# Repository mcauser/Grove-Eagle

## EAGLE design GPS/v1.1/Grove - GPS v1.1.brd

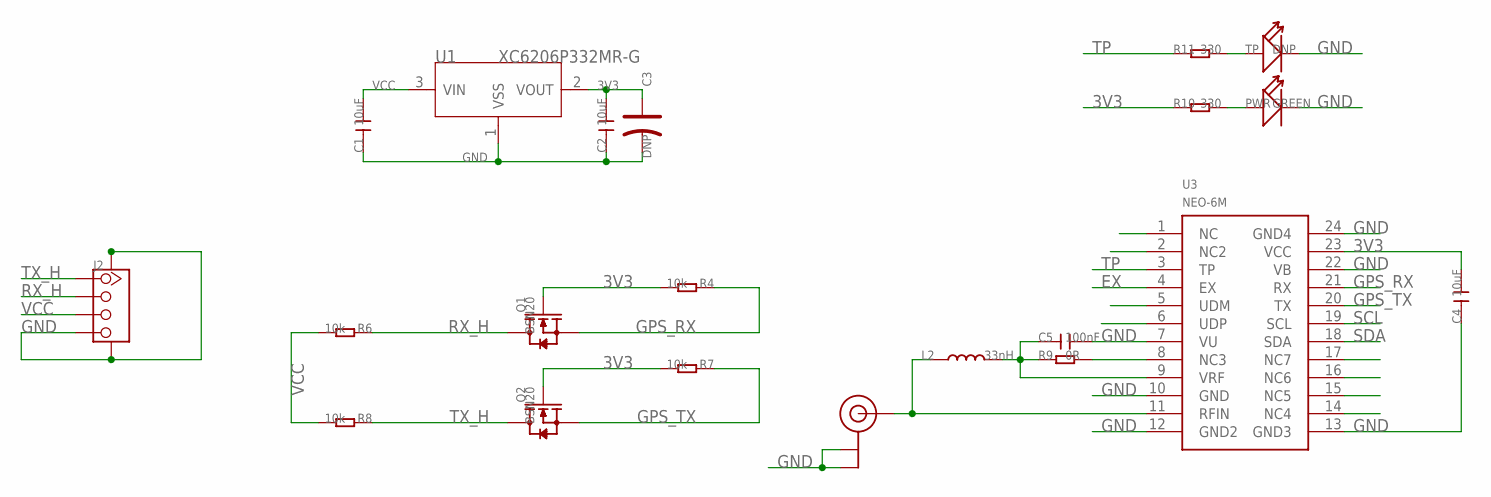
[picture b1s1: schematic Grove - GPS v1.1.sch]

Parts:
C1, C2, C4: 10uF; C0805
C3: DNP; AVX-A
C5: 100nF; C0603
J2: TWIG-4P-2.0-SMD-FEMALE-REINFORCE'DD'; 4P-SMD-2.0
L2: 33nH; L0603
PWR: GREEN; LED-0603
Q1, Q2: BSN20; SOT23
R4, R6, R7, R8: 10k; R0603
R9: 0R; R0603
R10, R11: 330; R0603
TP: DNP; LED-0603
U1: XC6206P332MR-G; SOT23
U3: NEO-6M; 28P-1.1-16.0X12.2
U4: U.FL

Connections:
3V3: C2.2, C3.+, C4.2, Q1.1 (G), Q2.1 (G), R4.2, R7.2, R10.1, U1.2 (VOUT), U3.23 (VCC)
EX: U3.4 (EX)
GND: C1.1, C2.1, C3.-, C4.1, C5.2, J2.4, J2.SS1, J2.SS2, PWR.-, TP.-, U1.1 (VSS), U3.7 (VU), U3.10 (GND), U3.12 (GND2), U3.13 (GND3), U3.22 (VB), U3.24 (GND4), U4.P$1 (GND), U4.P$2 (GND)
GPS_RX: Q1.2 (S), R4.1, U3.21 (RX)
GPS_TX: Q2.2 (S), R7.1, U3.20 (TX)
unnamed: L2.1, U3.11 (RFIN), U4.P$3 (SIGNAL)
unnamed: C5.1, L2.2, R9.1, U3.9 (VRF)
unnamed: PWR.+, R10.2
unnamed: R9.2, U3.8 (NC3)
unnamed: R11.2, TP.+
RX_H: J2.2, Q1.3 (D), R6.1
SCL: U3.19 (SCL)
SDA: U3.18 (SDA)
TP: R11.1, U3.3 (TP)
TX_H: J2.1, Q2.3 (D), R8.1
VCC: C1.2, J2.3, R6.2, R8.2, U1.3 (VIN)

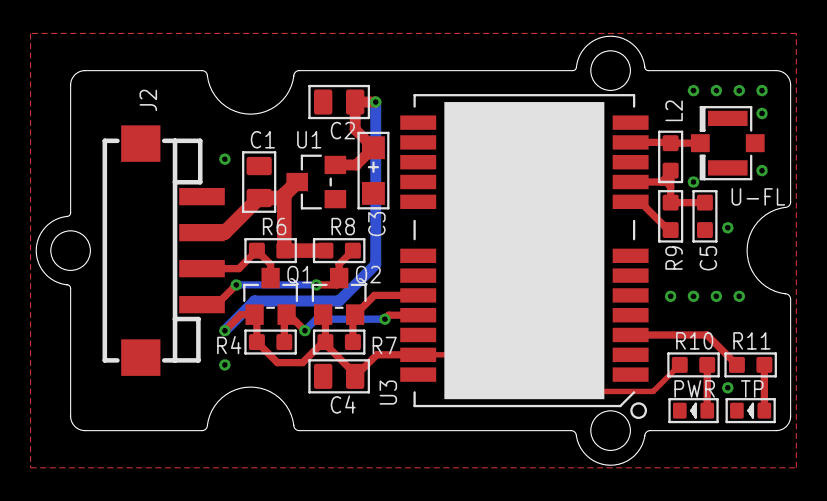
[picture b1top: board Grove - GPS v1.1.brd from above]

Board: 2 copper layers, 41.9 x 23.8 mm, 24 parts (2 on the bottom side), 13 nets.

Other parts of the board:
U$1: 2U-DIM-W/DRILL
U$2: OSHW_FILLX200_NOTEXT
U$4: TWIGLOGO

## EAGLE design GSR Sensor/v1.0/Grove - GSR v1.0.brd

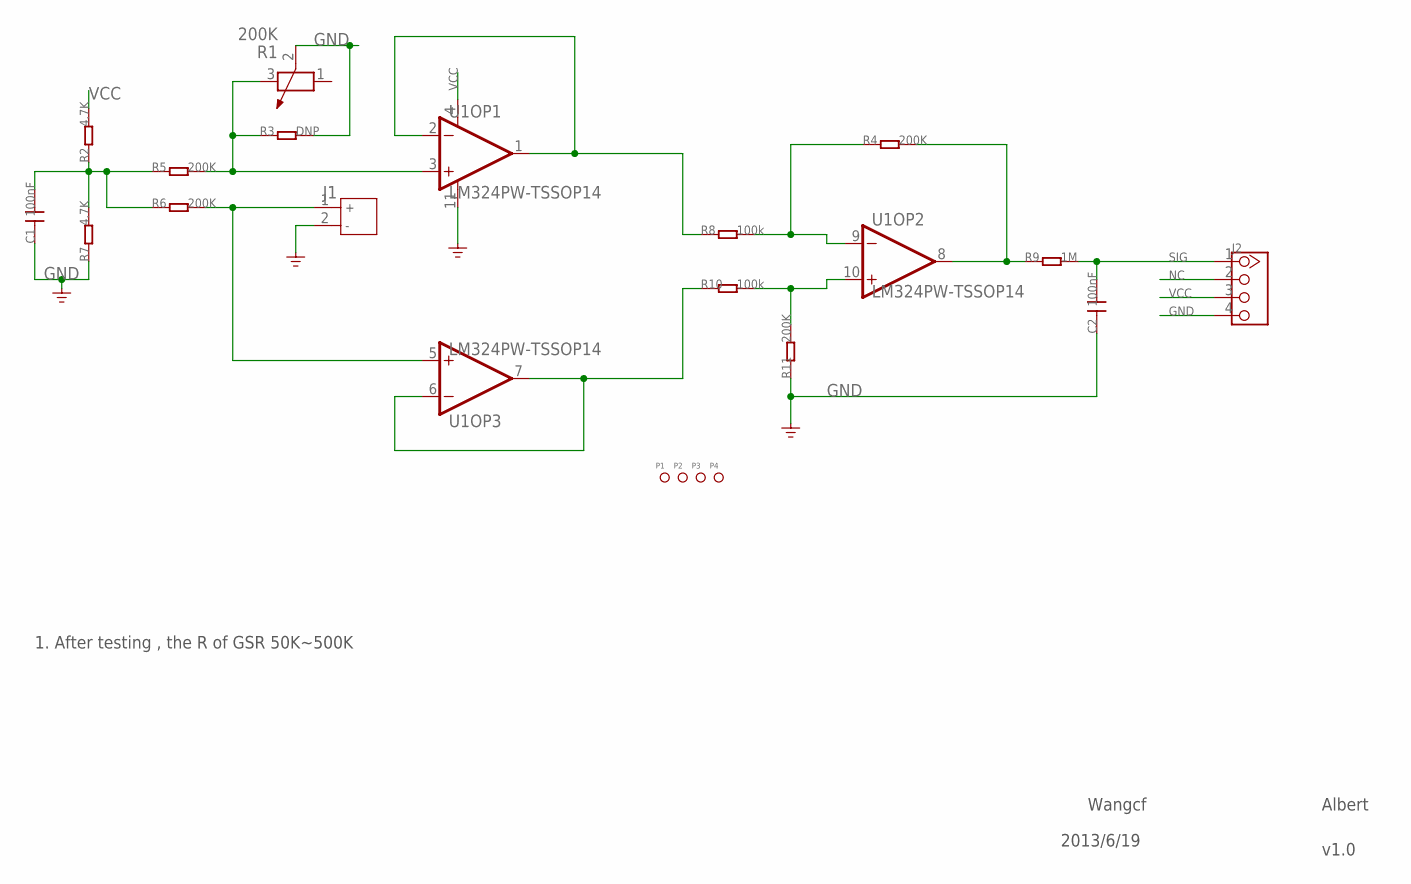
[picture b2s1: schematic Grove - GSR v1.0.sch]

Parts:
C1, C2: 100nF; 0603
J1: JACK-JST-2P-PW'2.0'; JST-2.0
J2: TWIG-4P-2.0-2.0; 4P-2.0
P1, P2, P3, P4: PAD-MARK; ROUND-MARK-1.0
R1: 200K; 3P-SMD-RECT-3.3X3.6
R2, R7: 4.7K; 0603
R3: DNP; 0603
R4, R5, R6, R11: 200K; 0603
R8, R10: 100k; 0603
R9: 1M; 0603
U1: LM324PW-TSSOP14; TSSOP14

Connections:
GND: C1.1, C2.1, J1.2, J2.4, R1.2 (3), R3.2, R7.1, R11.1, U1.11 (V-)
IN: J1.1, R6.2, U1.5 (IN+)
unnamed: R8.1, U1.1 (OUT), U1.2 (IN-)
unnamed: R10.1, U1.6 (IN-), U1.7 (OUT)
unnamed: R4.1, R8.2, U1.9 (IN-)
unnamed: R4.2, R9.1, U1.8 (OUT)
unnamed: R10.2, R11.2, U1.10 (IN+)
unnamed: C1.2, R2.1, R5.1, R6.1, R7.2
unnamed: R1.3 (2), R3.1, R5.2, U1.3 (IN+)
NC: J2.2
SIG: C2.2, J2.1, R9.2
VCC: J2.3, R2.2, U1.4 (V+)

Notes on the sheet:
1. After testing , the R of GSR 50K~500K
Wangcf
Albert
2013/6/19
v1.0

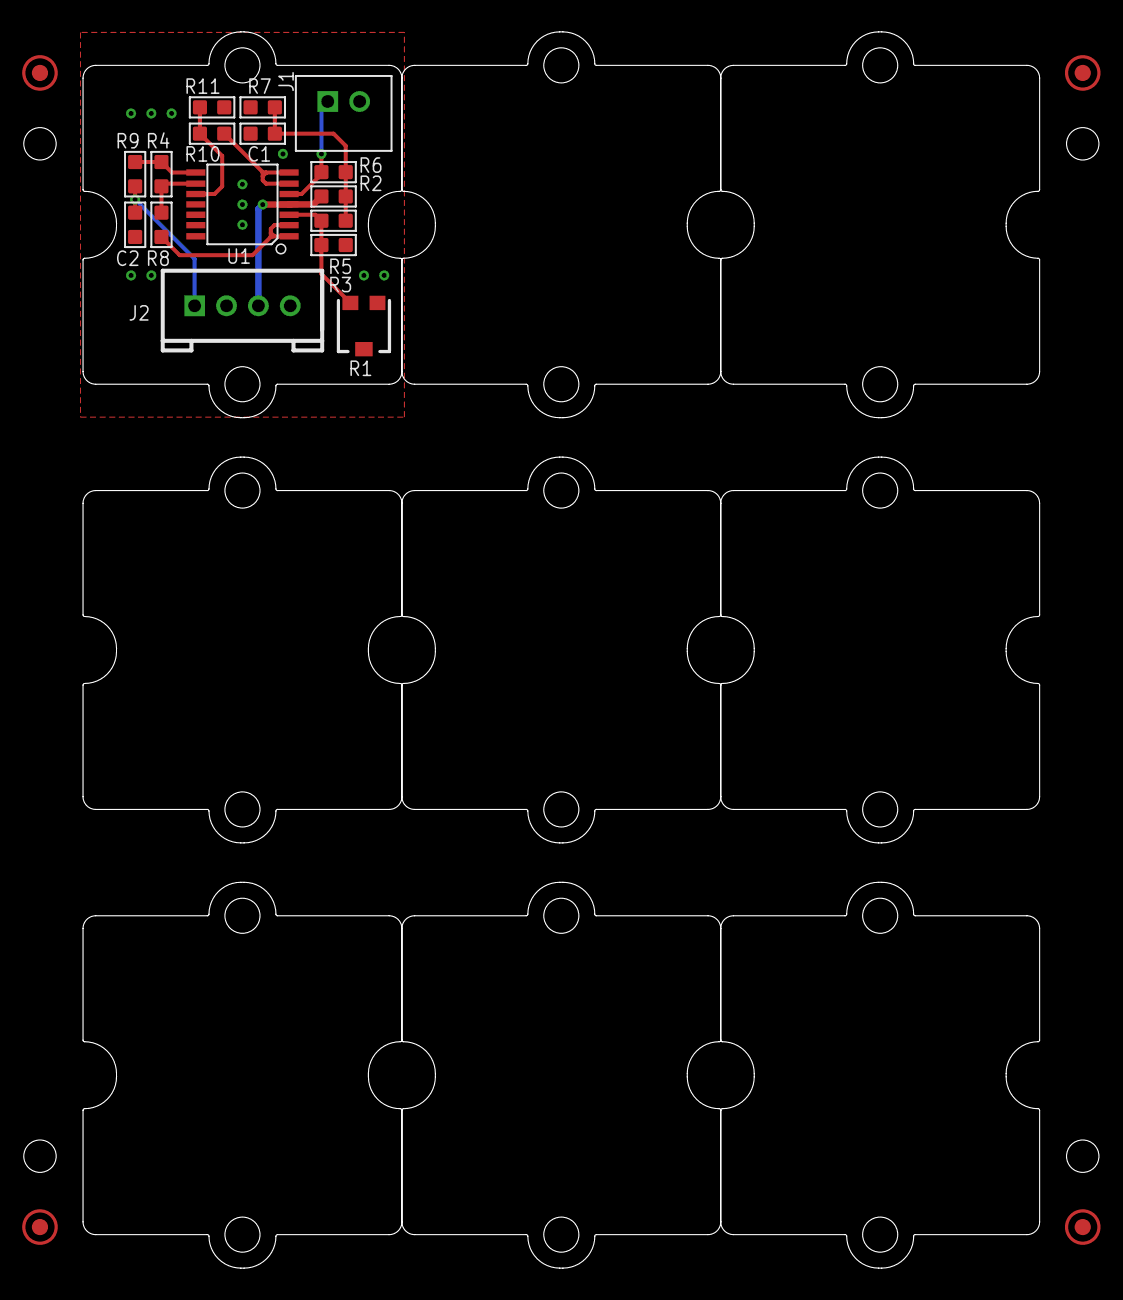
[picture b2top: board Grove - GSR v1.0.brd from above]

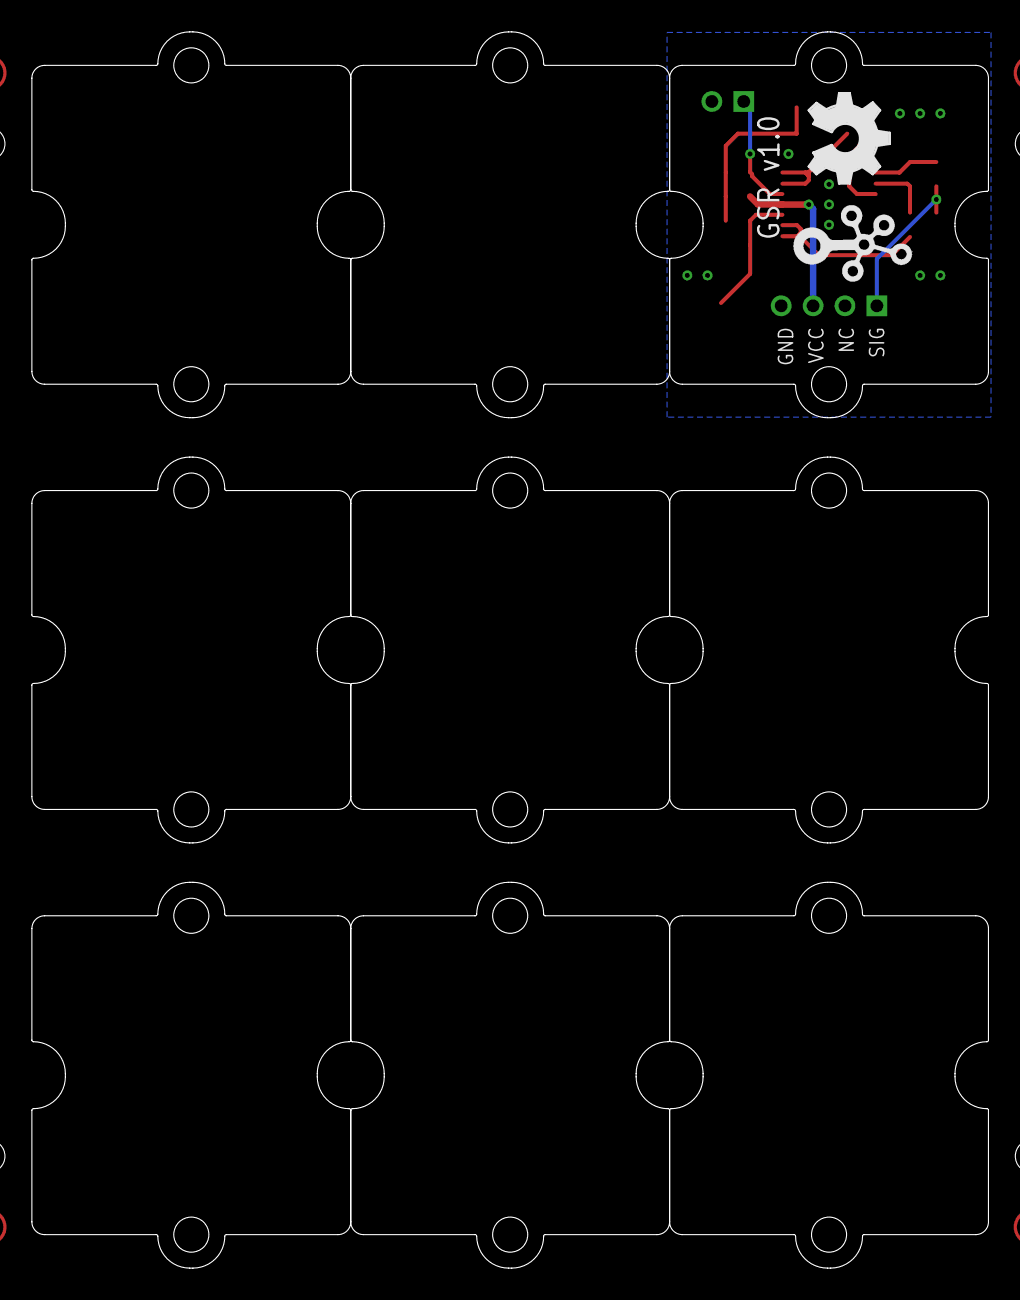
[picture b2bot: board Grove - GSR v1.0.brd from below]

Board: 2 copper layers, 60.0 x 77.5 mm, 31 parts (2 on the bottom side), 11 nets.

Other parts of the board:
U$5, U$9, U$10, U$12, U$13, U$14, U$15, U$16, U$17: 1U-DIM-W/-DRILL
U$7: TWIGLOGO
U$8: OSHW_FILLX200_NOTEXT

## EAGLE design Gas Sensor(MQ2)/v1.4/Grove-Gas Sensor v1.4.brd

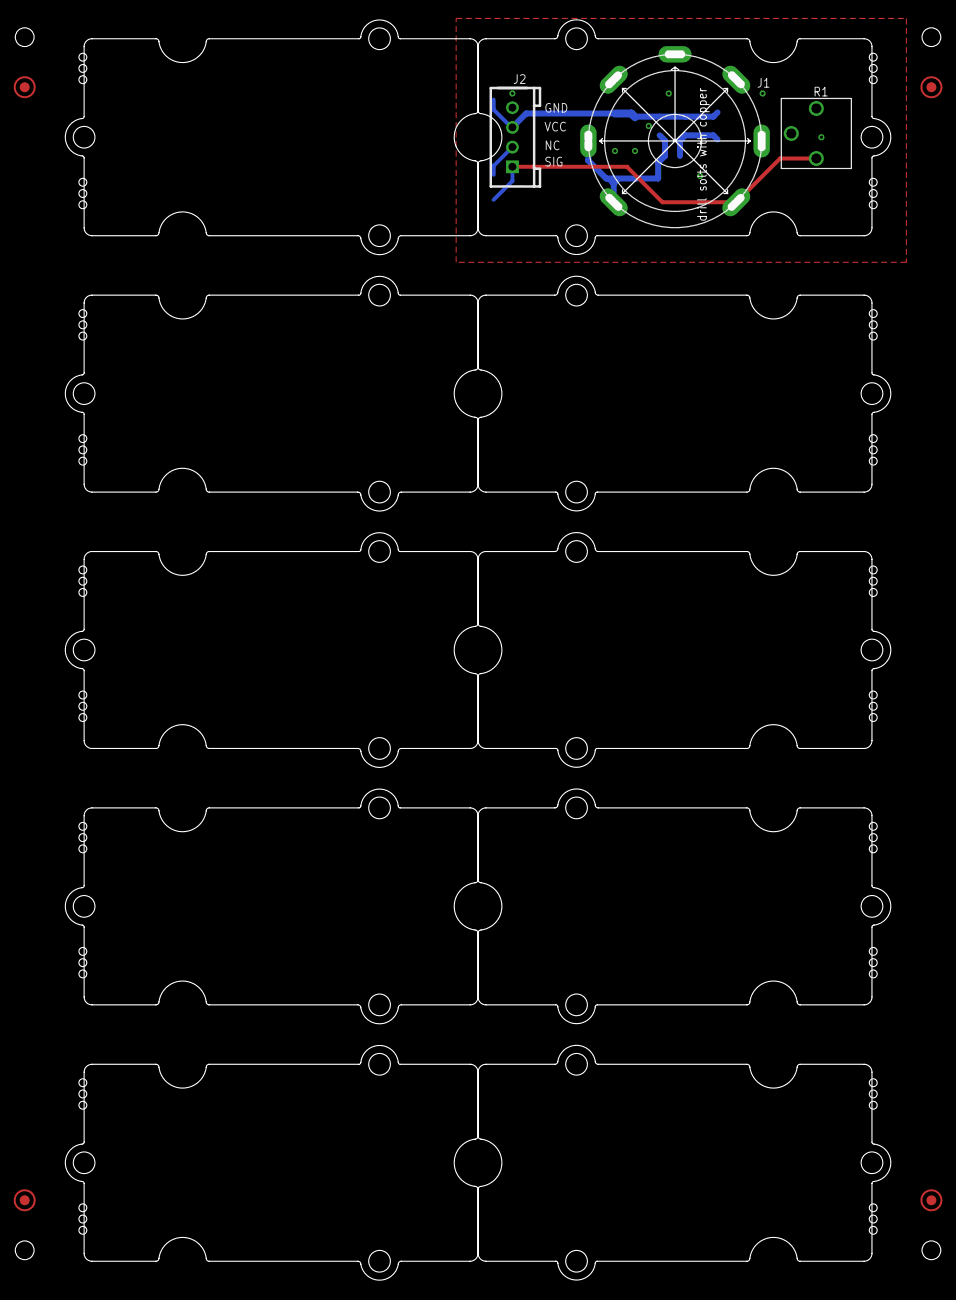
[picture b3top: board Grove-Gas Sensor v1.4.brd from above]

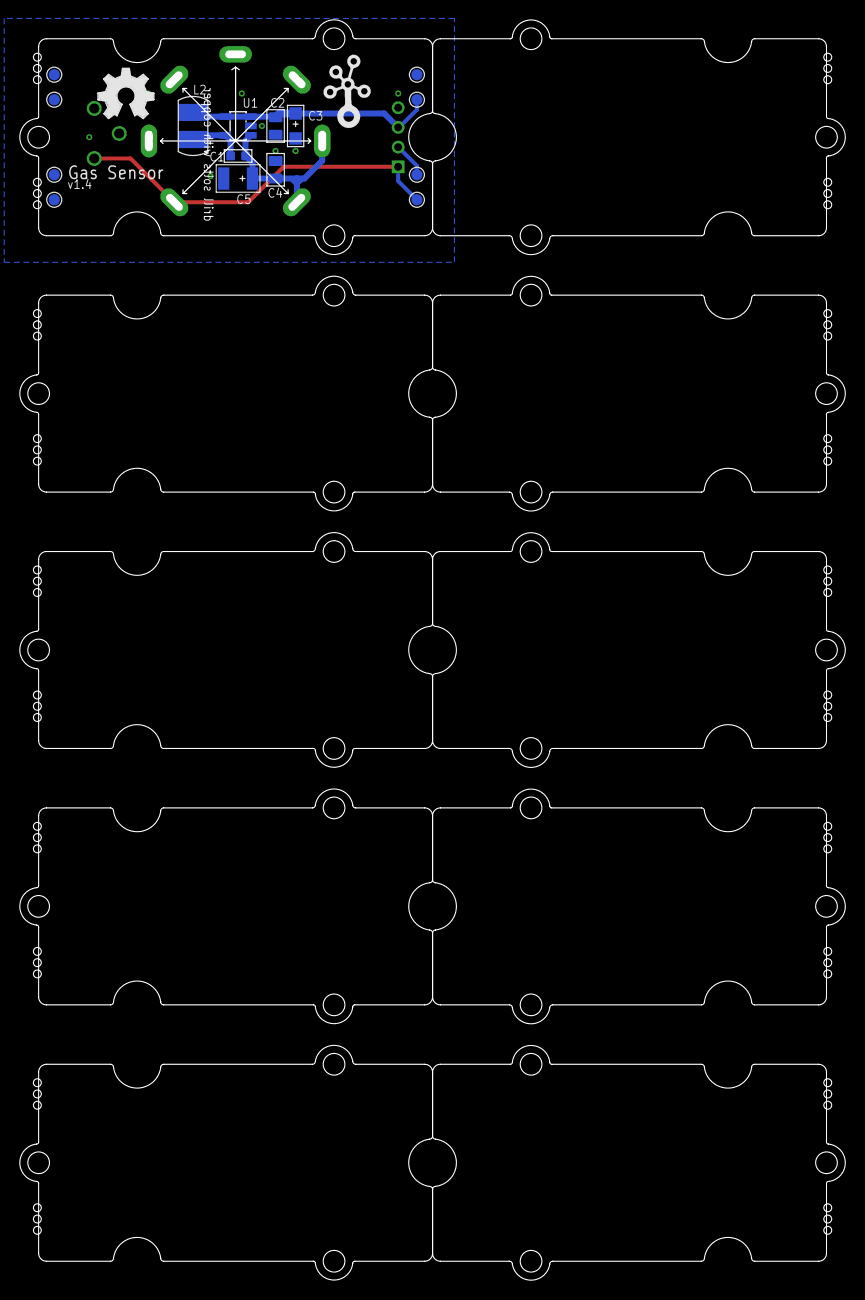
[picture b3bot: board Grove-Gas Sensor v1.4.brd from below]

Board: 2 copper layers, 83.8 x 128.0 mm, 34 parts (17 on the bottom side), 6 nets.

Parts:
C1: DNP; C0603
C2, C4: 10uF/25v; C0805
C3: DNP; AVX-A
C5: 100uF/6.3v; AVX-B
J1: Gas Sensor Socket; 6P-D17.6X9.8H
J2: 4P-LEADED-2.0
L2: CD32-100; SD32-4R7MC
P1, P2, P3, P4: ROUND-MARK-1.0
R1: 10K; PACKAGE__RESISTANCE
TP1, TP2, TP3, TP4, TP5, TP6, TP7, TP8: TP_4545
U1: SOT23-5
U$1: OSHW_FILLX200_NOTEXT
U$2, U$6, U$7, U$8, U$9, U$10, U$11, U$12, U$13, U$14: GROVE-TEST-PLATFORM
U$3: TWIGLOGO

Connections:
5V: C1.2, C4.1, C5.+, J1.1, J1.2, U1.1
GND: C2.2, C3.-, C4.2, C5.-, J1.5, J2.4, R1.2, TP4.T, U1.2
unnamed: C1.1, L2.2, U1.5
unnamed: J2.2, TP2.T
OUT: J1.6, J2.1, R1.3, TP1.T
VCC: C2.1, C3.+, J2.3, L2.1, TP3.T, U1.3, U1.4

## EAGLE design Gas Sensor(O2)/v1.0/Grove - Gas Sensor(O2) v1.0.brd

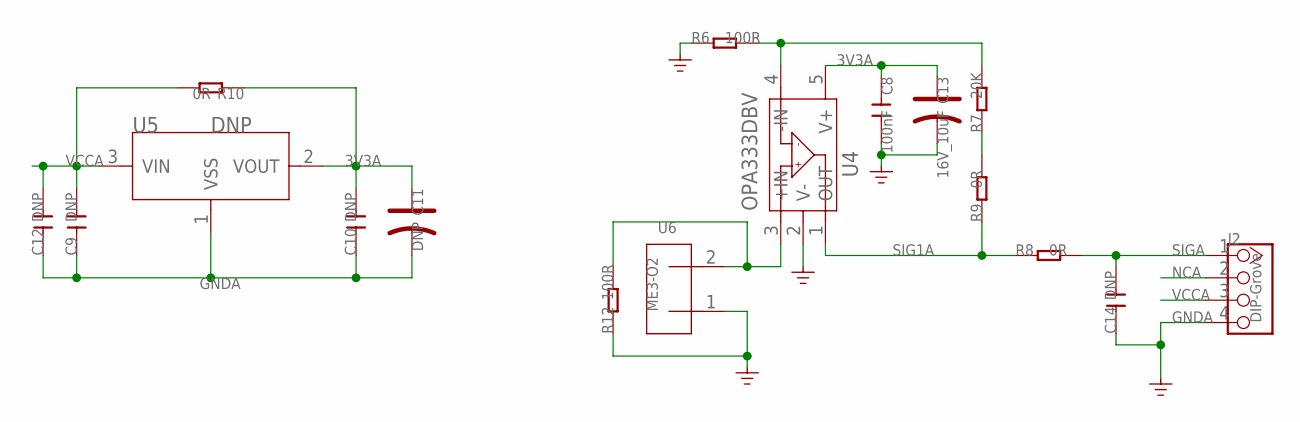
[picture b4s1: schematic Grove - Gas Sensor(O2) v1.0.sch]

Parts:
C8: 100nF; C0603
C9, C10: DNP; C0603
C11: DNP; AVX-A
C12, C14: DNP; C0805
C13: 16V_10uF; AVX-A
J2: DIP-Grove; 4P-2.0
R6, R12: 100R; R0603
R7: 20K; R0603
R8, R9, R10: 0R; R0603
U4: OPA333DBV; SOT23-5
U5: DNP; SOT23
U6: ME3-O2; 2P-D20X16H

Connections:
3V3A: C8.1, C10.2, C11.+, C13.+, R10.1, U4.5 (V+), U5.2 (VOUT)
GNDA: C8.2, C9.1, C10.1, C11.-, C12.1, C13.-, C14.1, J2.4, R6.1, R12.1, U4.2 (V-), U5.1 (VSS), U6.1
unnamed: R12.2, U4.3 (+IN), U6.2
unnamed: R6.2, R7.2, U4.4 (-IN)
unnamed: R7.1, R9.2
NCA: J2.2
SIG1A: R8.1, R9.1, U4.1 (OUT)
SIGA: C14.2, J2.1, R8.2
VCCA: C9.2, C12.2, J2.3, R10.2, U5.3 (VIN)

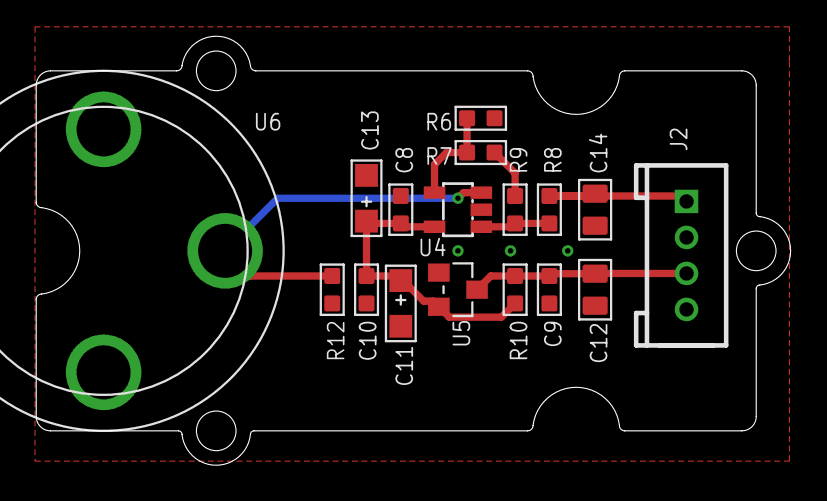
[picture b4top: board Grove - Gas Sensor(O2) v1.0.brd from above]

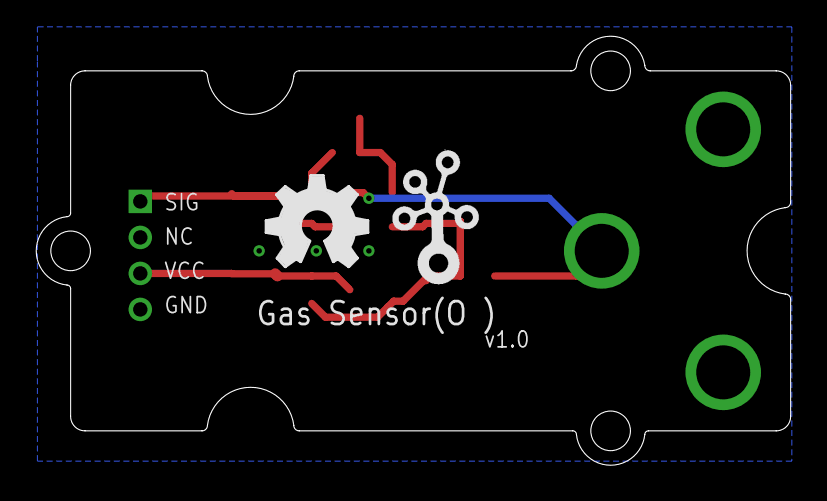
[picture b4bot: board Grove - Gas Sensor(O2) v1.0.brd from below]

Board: 2 copper layers, 41.9 x 23.8 mm, 20 parts (2 on the bottom side), 8 nets.

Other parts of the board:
U$1: 2U-DIM-W/DRILL
U$15: OSHW_FILLX200_NOTEXT
U$17: TWIGLOGO

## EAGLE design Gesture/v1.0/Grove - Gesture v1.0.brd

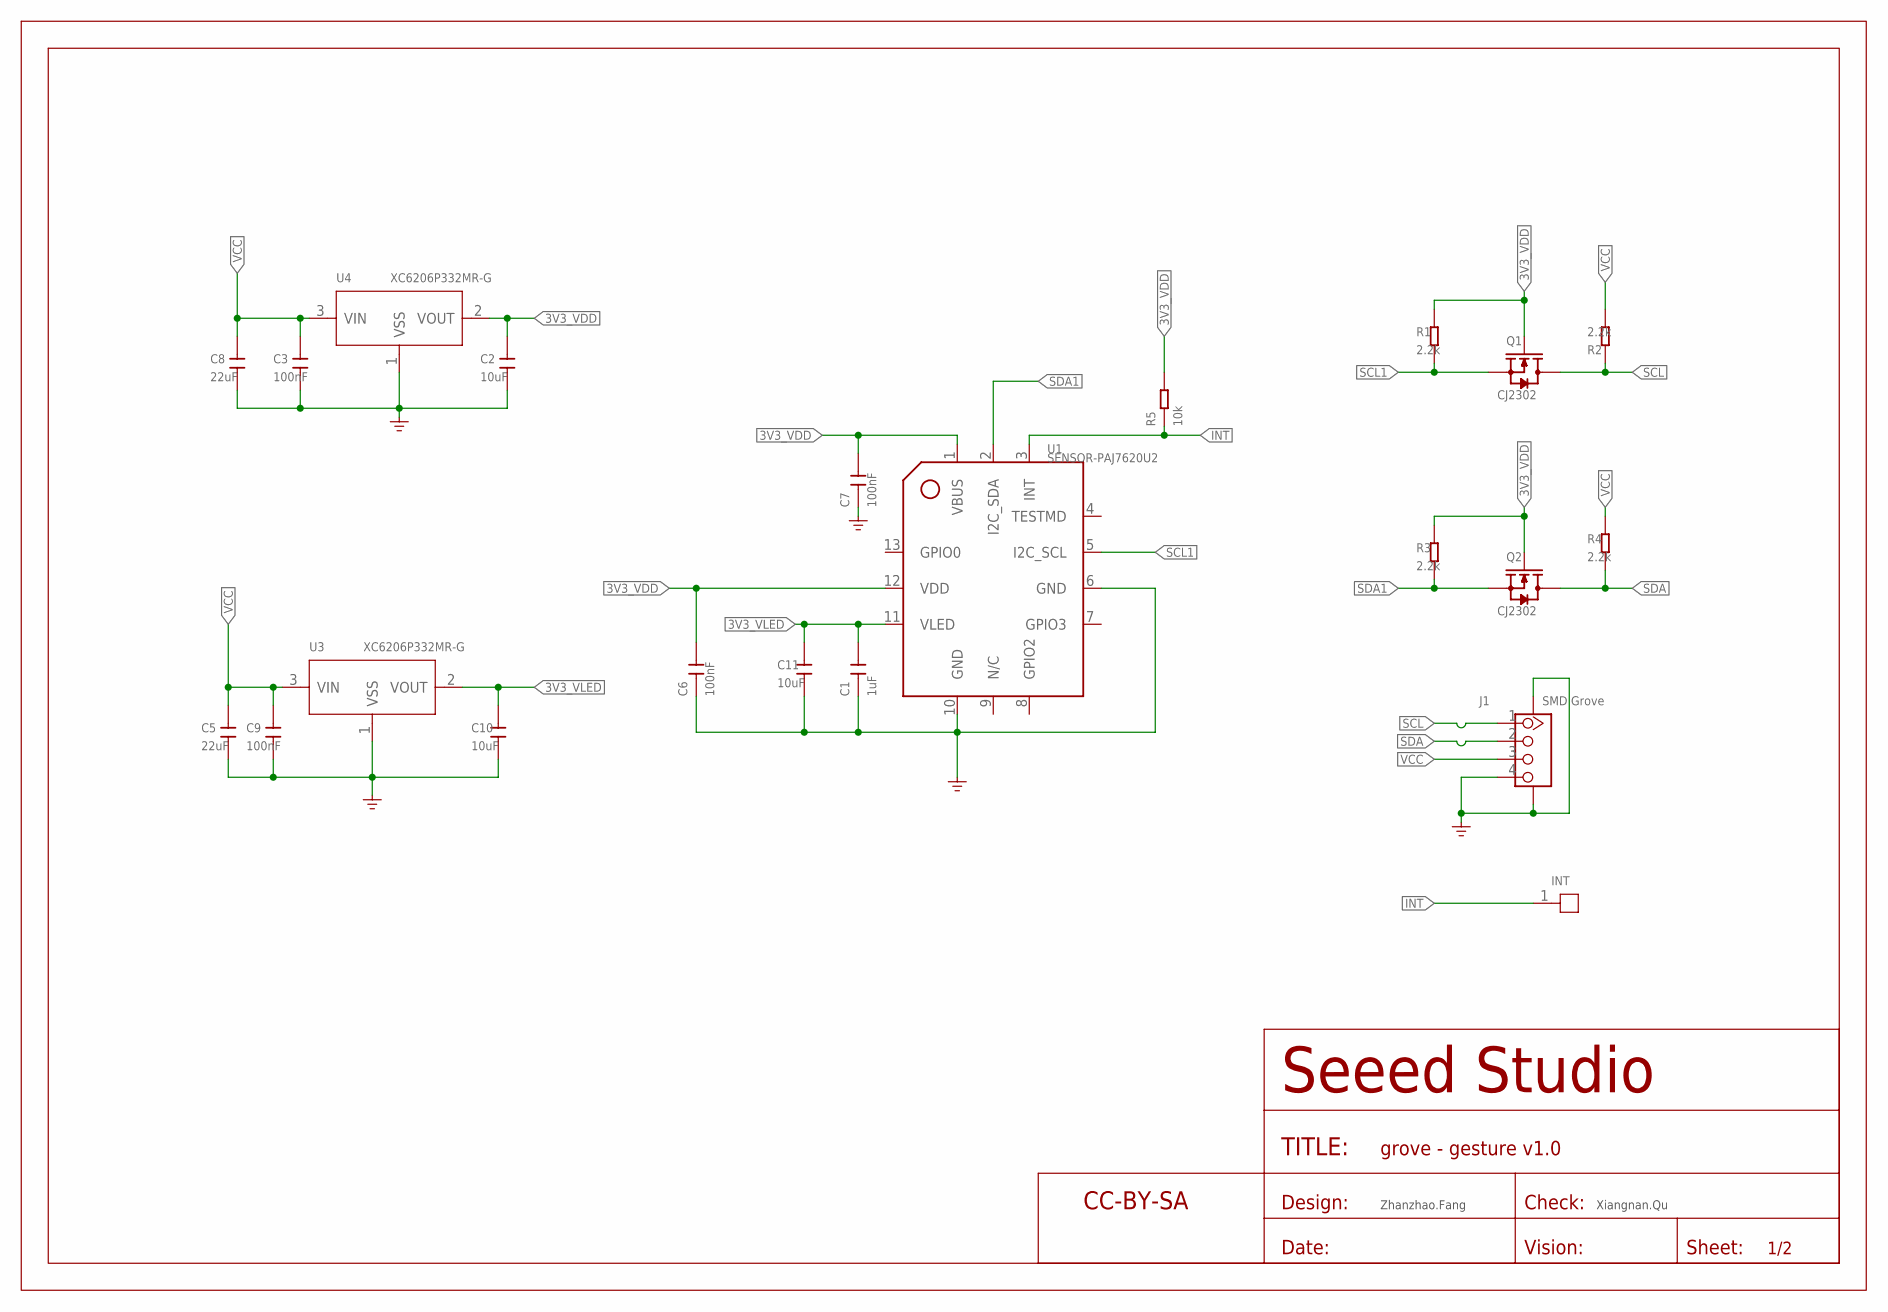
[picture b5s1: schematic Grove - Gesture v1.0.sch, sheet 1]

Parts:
C1: 1uF; C0603
C2, C10, C11: 10uF; C0603
C3, C6, C7, C9: 100nF; C0603
C5, C8: 22uF; C0805
INT: DNP; 1P-80/40MIL
J1: SMD Grove; HW4-SMD-2.0-90D
Q1, Q2: CJ2302; SOT-23
R1, R2, R3, R4: 2.2k; R0603
R5: 10k; R0603
U1: SENSOR-PAJ7620U2; LGA13-SMD-L5.2*W3*H2MM
U3, U4: XC6206P332MR-G; SOT-23
U$4: SEEEDSTUDIO-OPEN-SCH-FRAME; SEEEDSTUDIO-PCB-FRAME

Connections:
3V3_VDD: C2.2, C6.2, C7.2, Q1.1 (G), Q2.1 (G), R1.2, R3.2, R5.2, U1.1 (VBUS), U1.12 (VDD), U4.2 (VOUT)
3V3_VLED: C1.2, C10.2, C11.2, U1.11 (VLED), U3.2 (VOUT)
GND: C1.1, C2.1, C3.1, C5.1, C6.1, C7.1, C8.1, C9.1, C10.1, C11.1, J1.4, J1.SS1, J1.SS2, U1.6 (GND), U1.10 (GND), U3.1 (VSS), U4.1 (VSS)
INT: INT.1, R5.1, U1.3 (INT)
SCL: J1.1, Q1.3 (D), R2.1
SCL1: Q1.2 (S), R1.1, U1.5 (I2C_SCL)
SDA: J1.2, Q2.3 (D), R4.1
SDA1: Q2.2 (S), R3.1, U1.2 (I2C_SDA)
VCC: C3.2, C5.2, C8.2, C9.2, J1.3, R2.2, R4.2, U3.3 (VIN), U4.3 (VIN)

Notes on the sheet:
Zhanzhao.Fang
Xiangnan.Qu

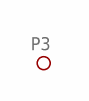
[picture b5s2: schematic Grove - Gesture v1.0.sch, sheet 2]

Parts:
P3: PAD-MARK'ANNULAR'; ROUND-MARK-1.0

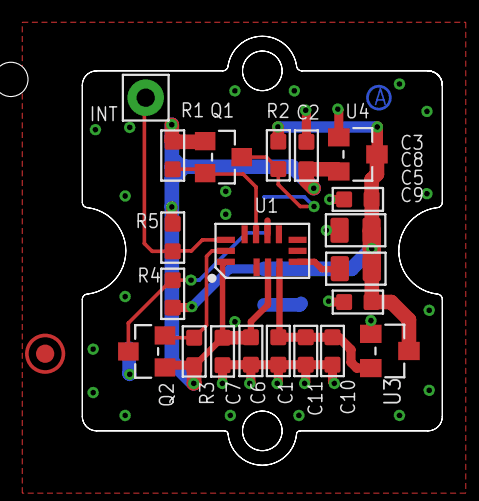
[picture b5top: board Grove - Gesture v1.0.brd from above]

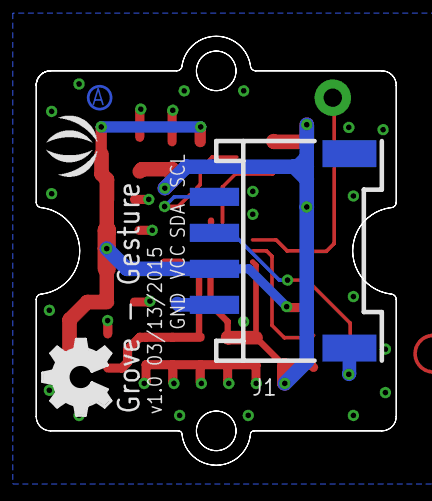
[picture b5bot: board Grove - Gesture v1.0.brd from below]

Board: 2 copper layers, 20.0 x 23.8 mm, 28 parts (3 on the bottom side), 9 nets.

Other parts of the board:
U$1: OSHW_FILLX150_NOTEXT
U$5, U$6: GROVE-1*1-TEST-PLATFORM
U$15: SEEED-SILK-160*153MIL

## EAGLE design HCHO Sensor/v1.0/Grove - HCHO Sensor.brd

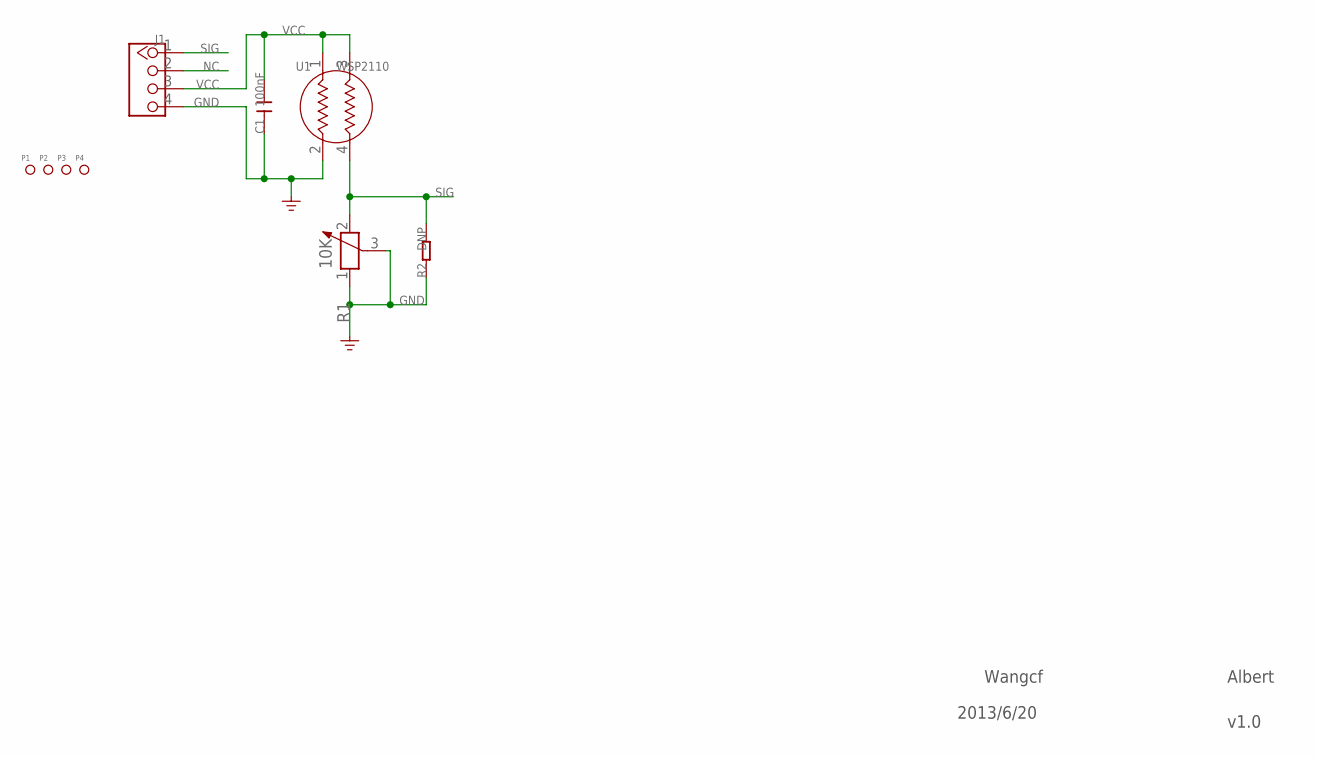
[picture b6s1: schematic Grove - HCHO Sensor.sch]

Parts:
C1: 100nF; C0603
J1: TWIG-4P-2.0-2.0; 4P-2.0
P1, P2, P3, P4: PAD-MARK; ROUND-MARK-1.0
R1: 10K; 3P-SQUA-7X6.8
R2: DNP; R0603
U1: WSP2110; 4P-D9.4-7.5H

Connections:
GND: C1.1, J1.4, R1.1, R1.3, R2.1, U1.2
NC: J1.2
SIG: J1.1, R1.2, R2.2, U1.4
VCC: C1.2, J1.3, U1.1, U1.3

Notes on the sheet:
Wangcf
Albert
2013/6/20
v1.0

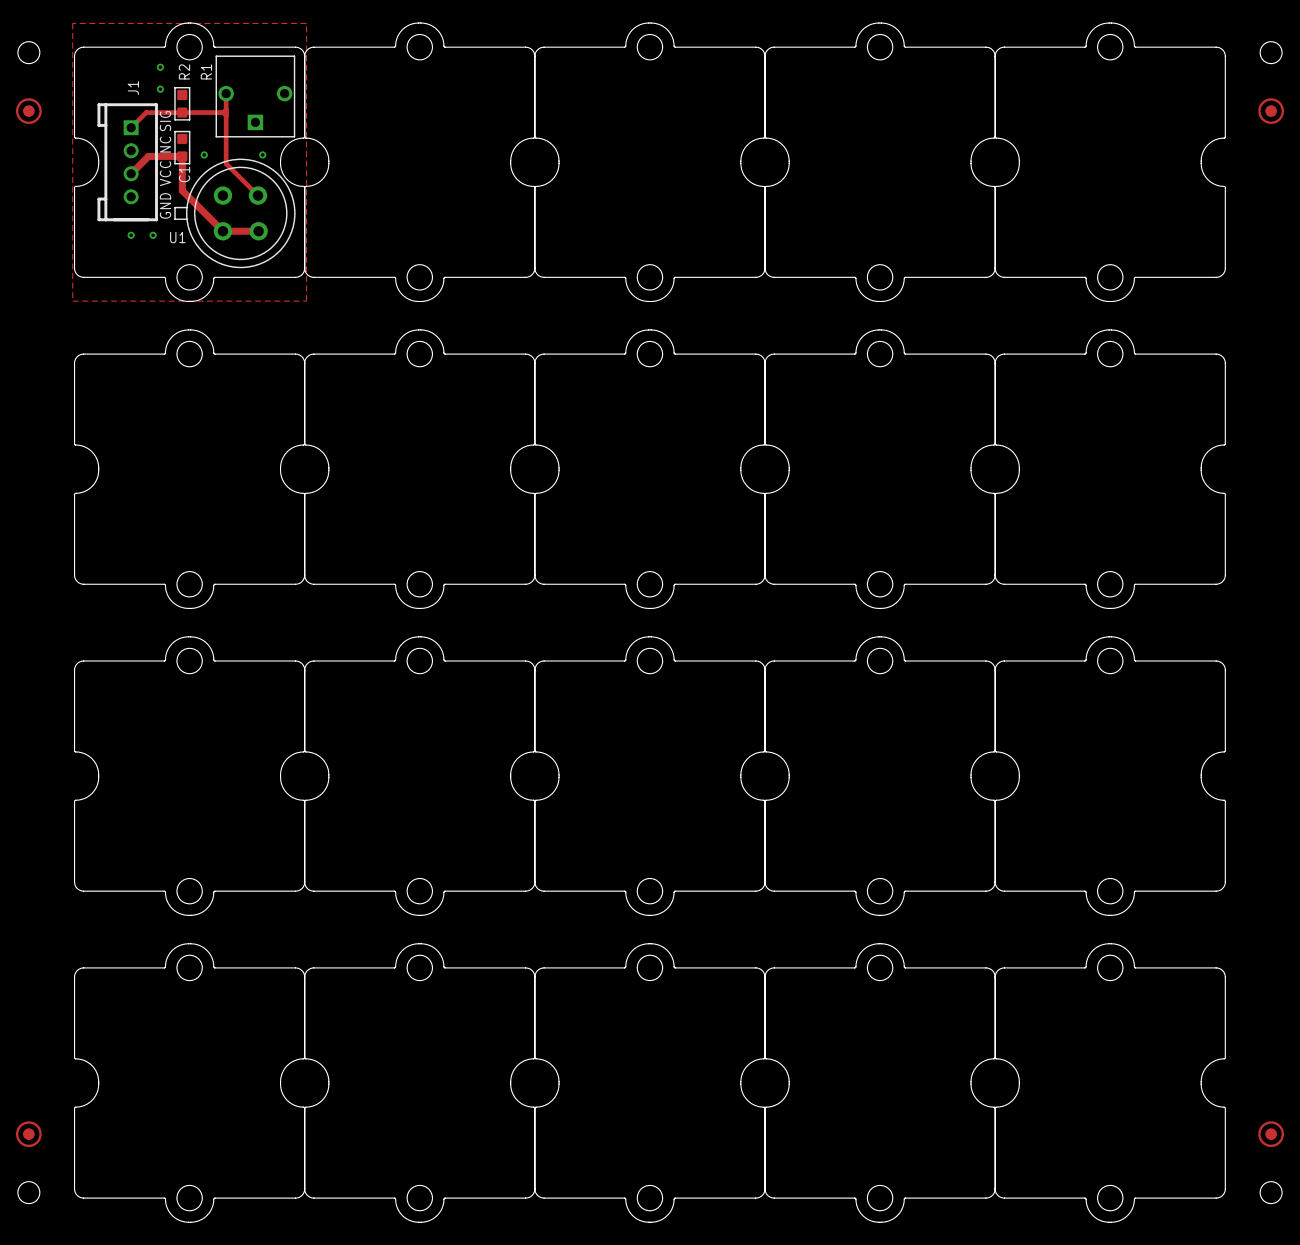
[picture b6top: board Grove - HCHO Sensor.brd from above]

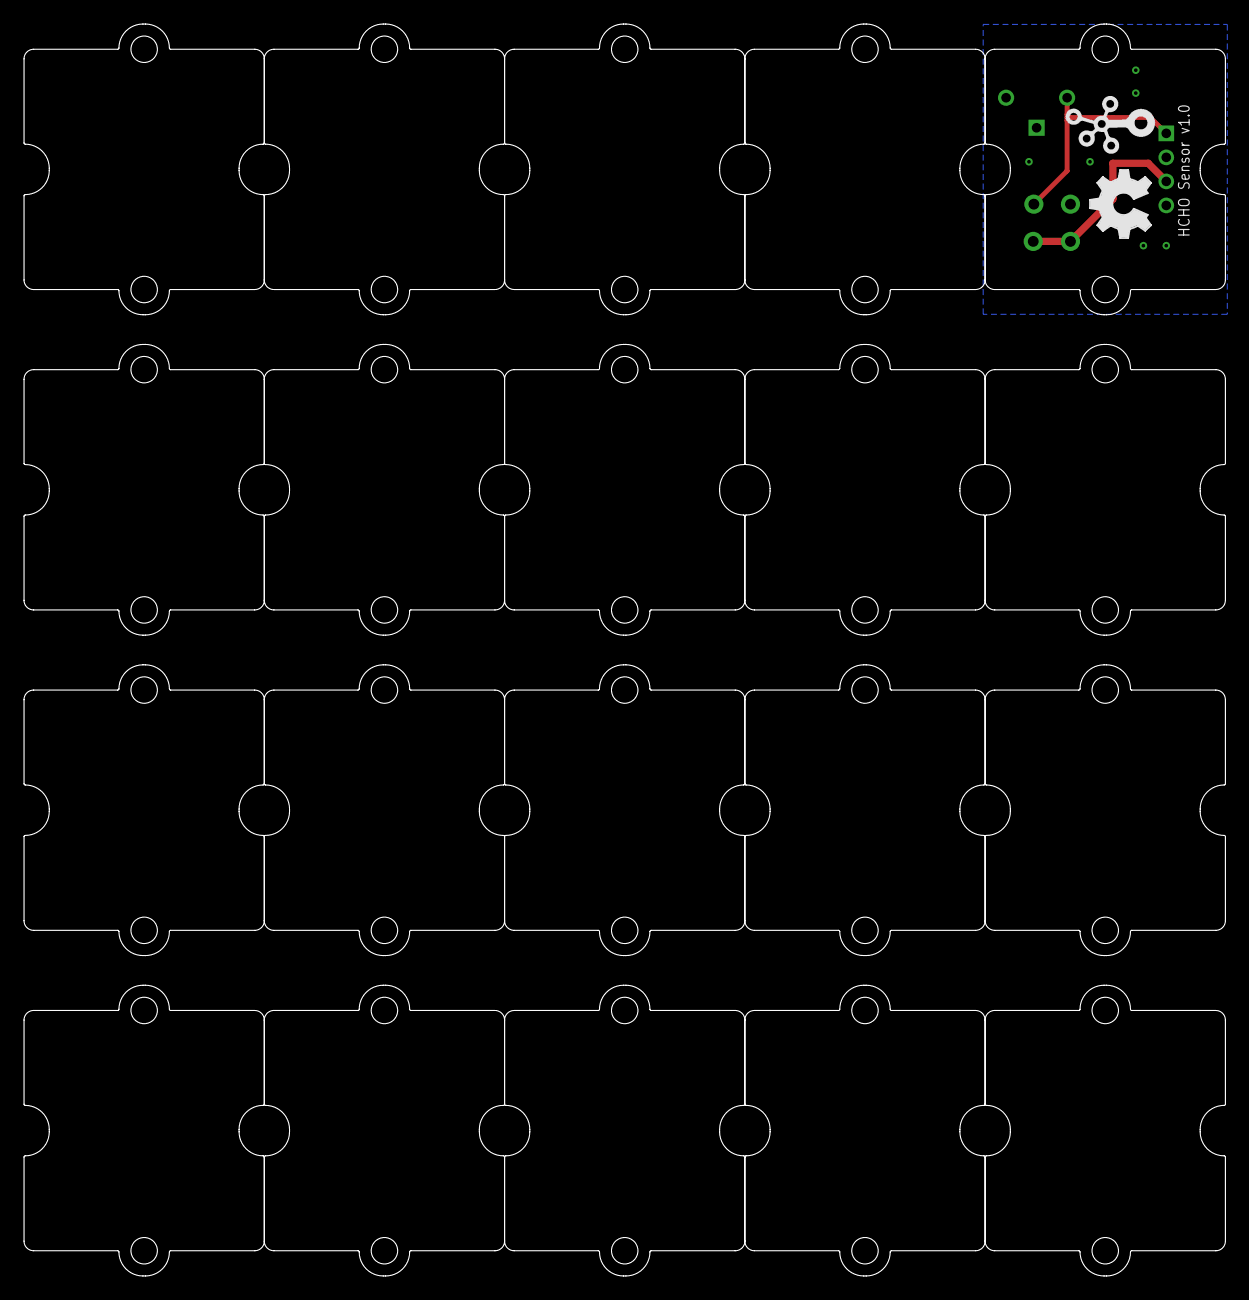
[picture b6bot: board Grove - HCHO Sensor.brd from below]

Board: 2 copper layers, 100.0 x 104.2 mm, 31 parts (2 on the bottom side), 3 nets.

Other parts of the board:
U$4: OSHW_FILLX200_NOTEXT
U$5, U$7, U$8, U$9, U$10, U$11, U$12, U$13, U$14, U$15, U$16, U$17, U$18, U$19, U$20, U$21, U$22, U$23, U$24, U$25: 1U-DIM-W/-DRILL
U$6: TWIGLOGO

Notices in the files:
parts and their libraries:
moudle-new: This work is licensed under the Creative Commons Attribution 4.0 International License.
To view a copy of this license,visit:
http://creativecommons.org/licenses/by-sa/4.0
moudle-new: CC-BY-SA
